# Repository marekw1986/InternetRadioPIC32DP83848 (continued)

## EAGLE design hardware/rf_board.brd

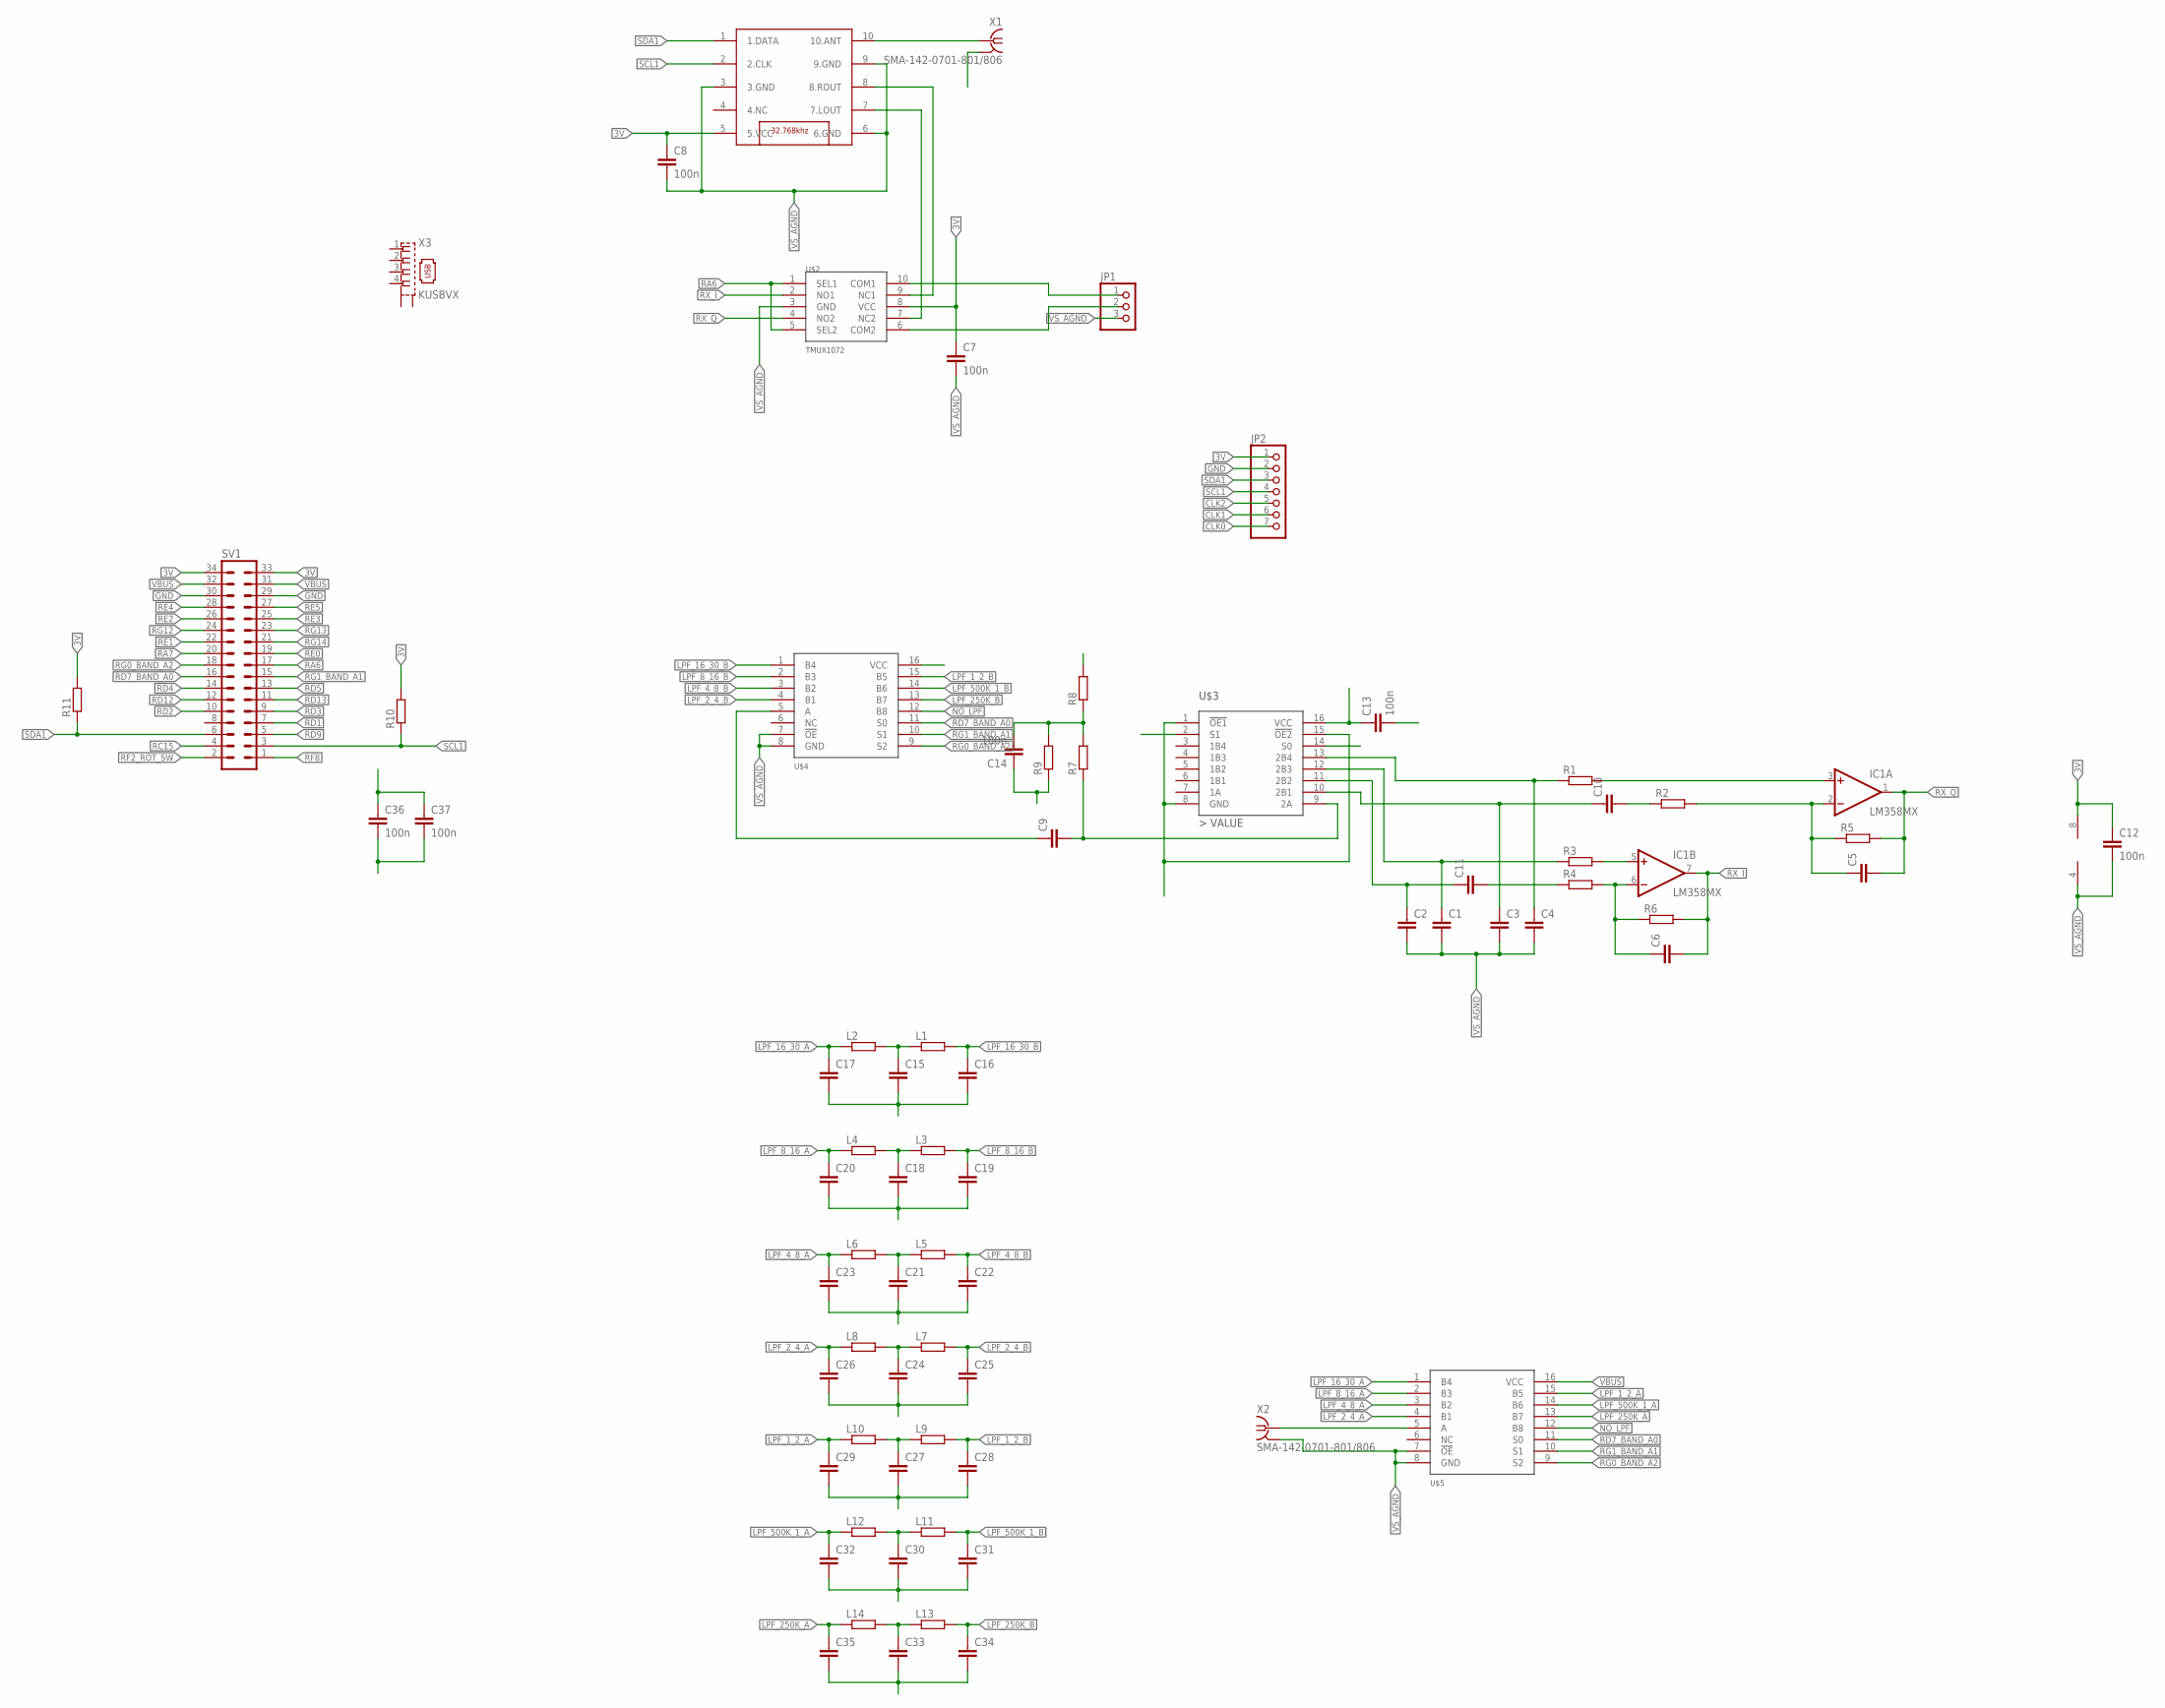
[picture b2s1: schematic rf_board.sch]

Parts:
C1, C2, C3, C4, C5, C6, C9, C10, C11: C-EUC0603; C0603
C7: 100n; C1206
C8, C12, C13, C14, C36, C37: 100n; C0603
C15, C16, C17, C18, C19, C20, C21, C22, C23, C24, C25, C26, C27, C28, C29, C30, C31, C32, C33, C34, C35: C-EUC0805; C0805
IC1: LM358MX; SO08
JP1: PINHD-1X3; 1X03
JP2: PINHD-1X7; 1X07
L1, L2, L3, L4, L5, L6, L7, L8, L9, L10, L11, L12, L13, L14: R-EU_R0805; R0805
R1, R2, R3, R4, R5, R6, R8, R9: R-EU_R0603; R0603
R7, R11: R-EU_0204/5; 0204/5
R10: R-EU_0204/7; 0204/7
SV1: ML34L
U$1: TEA5767; TJ-102BC
U$2: TMUX1072; TSSOP8
U$3: FST3253SO16; SO16
U$4, U$5: SN74CBT3251; TSSOP16
X1, X2: SMA-142-0701-801/806; J502-ND-142-0701-801/806
X3: KUSBVX

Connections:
3V: C7.1, C8.1, C12.1, C13.1, IC1.8 (V+), JP2.1, R8.2, R10.2, R11.2, SV1.33, SV1.34, U$1.5 (5.VCC), U$2.8 (VCC), U$3.16 (VCC)
CLK0: JP2.7, U$3.14 (S0)
CLK1: JP2.6, U$3.2 (S1)
CLK2: JP2.5
GND: JP2.2, SV1.29, SV1.30
IN_LEFT: JP1.2, U$2.6 (COM2)
IN_RIGHT: JP1.1, U$2.10 (COM1)
LPF_1_2_A: C29.1, L10.1, U$5.15 (B5)
LPF_1_2_B: C28.1, L9.2, U$4.15 (B5)
LPF_2_4_A: C26.1, L8.1, U$5.4 (B1)
LPF_2_4_B: C25.1, L7.2, U$4.4 (B1)
LPF_4_8_A: C23.1, L6.1, U$5.3 (B2)
LPF_4_8_B: C22.1, L5.2, U$4.3 (B2)
LPF_8_16_A: C20.1, L4.1, U$5.2 (B3)
LPF_8_16_B: C19.1, L3.2, U$4.2 (B3)
LPF_16_30_A: C17.1, L2.1, U$5.1 (B4)
LPF_16_30_B: C16.1, L1.2, U$4.1 (B4)
LPF_250K_A: C35.1, L14.1, U$5.13 (B7)
LPF_250K_B: C34.1, L13.2, U$4.13 (B7)
LPF_500K_1_A: C32.1, L12.1, U$5.14 (B6)
LPF_500K_1_B: C31.1, L11.2, U$4.14 (B6)
unnamed: IC1.3 (+IN), R1.2
unnamed: C3.1, C10.1, U$3.10 (2B1)
unnamed: C4.1, R1.1, U$3.13 (2B4)
unnamed: C1.1, R3.1, U$3.12 (2B3)
unnamed: C2.1, C11.1, U$3.11 (2B2)
unnamed: C5.1, IC1.2 (-IN), R2.2, R5.1
unnamed: IC1.5 (+IN), R3.2
unnamed: C6.1, IC1.6 (-IN), R4.2, R6.1
unnamed: C9.2, R7.1, U$3.9 (2A)
unnamed: U$1.8 (8.ROUT), U$2.9 (NC1)
unnamed: U$1.7 (7.LOUT), U$2.7 (NC2)
unnamed: C10.2, R2.1
unnamed: C11.2, R4.1
unnamed: C14.2, R7.2, R8.1, R9.2
unnamed: C15.1, L1.1, L2.2
unnamed: U$5.5 (A), X2.1
unnamed: U$1.10 (10.ANT), X1.1
unnamed: C18.1, L3.1, L4.2
unnamed: C21.1, L5.1, L6.2
unnamed: C24.1, L7.1, L8.2
unnamed: C27.1, L9.1, L10.2
unnamed: C30.1, L11.1, L12.2
unnamed: C33.1, L13.1, L14.2
unnamed: C9.1, U$4.5 (A)
NO_LPF: U$4.12 (B8), U$5.12 (B8)
RA6: SV1.17, U$2.1 (SEL1), U$2.5 (SEL2)
RA7: SV1.20
RC15: SV1.4
RD1: SV1.7
RD2: SV1.10
RD3: SV1.9
RD4: SV1.14
RD5: SV1.13
RD7_BAND_A0: SV1.16, U$4.11 (S0), U$5.11 (S0)
RD9: SV1.5
RD12: SV1.12
RD13: SV1.11
RE0: SV1.19
RE1: SV1.22
RE2: SV1.26
RE3: SV1.25
RE4: SV1.28
RE5: SV1.27
RF2_ROT_SW: SV1.2
RF8: SV1.1
RG0_BAND_A2: SV1.18, U$4.9 (S2), U$5.9 (S2)
RG1_BAND_A1: SV1.15, U$4.10 (S1), U$5.10 (S1)
RG12: SV1.24
RG13: SV1.23
RG14: SV1.21
RX_I: C6.2, IC1.7 (OUT), R6.2, U$2.2 (NO1)
RX_Q: C5.2, IC1.1 (OUT), R5.2, U$2.4 (NO2)
SCL1: JP2.4, R10.1, SV1.3, U$1.2 (2.CLK)
SDA1: JP2.3, R11.1, SV1.6, U$1.1 (1.DATA)
VBUS: C36.1, C37.1, SV1.31, SV1.32, U$4.16 (VCC), U$5.16 (VCC)
VS_AGND: C1.2, C2.2, C3.2, C4.2, C7.2, C8.2, C12.2, C13.2, C14.1, C15.2, C16.2, C17.2, C18.2, C19.2, C20.2, C21.2, C22.2, C23.2, C24.2, C25.2, C26.2, C27.2, C28.2, C29.2, C30.2, C31.2, C32.2, C33.2, C34.2, C35.2, C36.2, C37.2, IC1.4 (V-), JP1.3, R9.1, U$1.3 (3.GND), U$1.6 (6.GND), U$1.9 (9.GND), U$2.3 (GND), U$3.1 (!OE1), U$3.8 (GND), U$3.15 (!OE2), U$4.7 (!OE), U$4.8 (GND), U$5.7 (!OE), U$5.8 (GND), X1.G@1 (2), X1.G@2 (2), X1.G@3 (2), X1.G@4 (2), X2.G@1 (2), X2.G@2 (2), X2.G@3 (2), X2.G@4 (2)

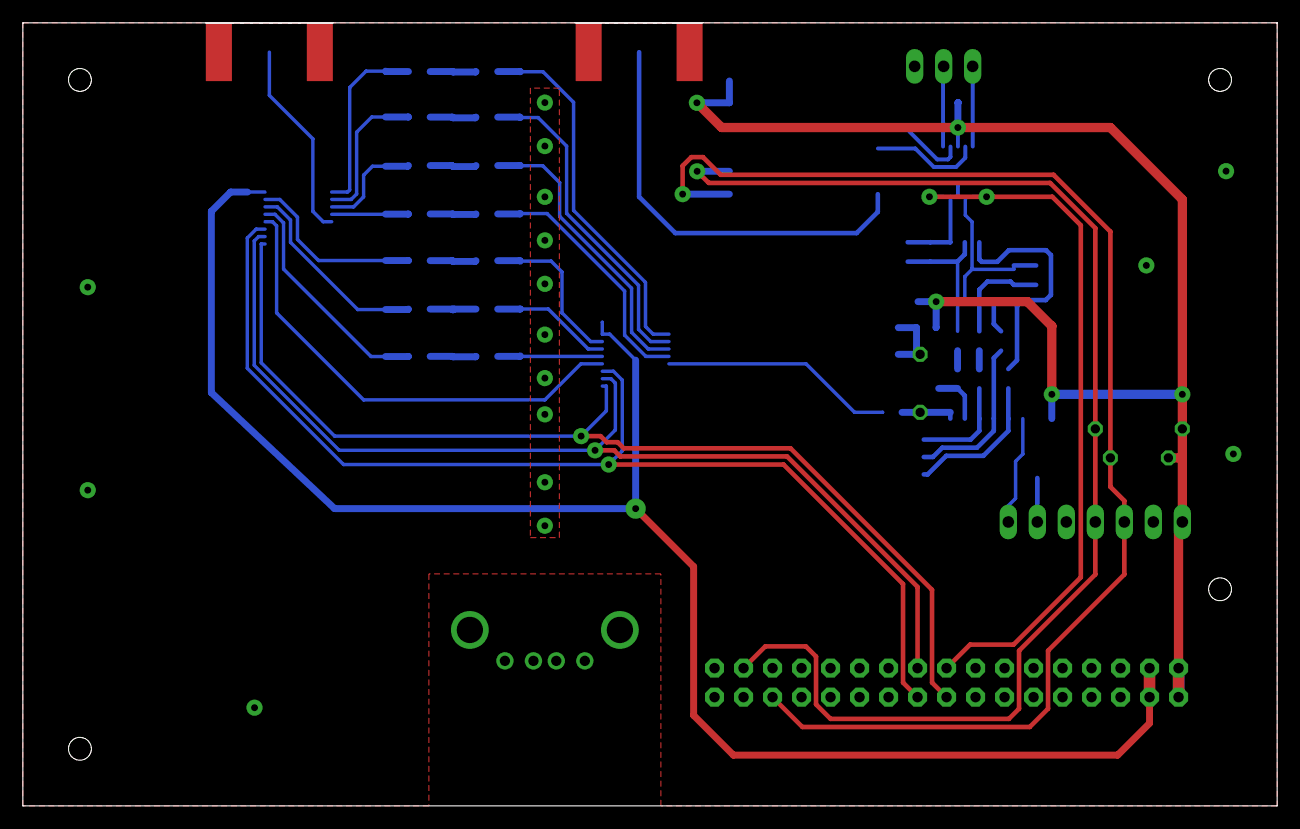
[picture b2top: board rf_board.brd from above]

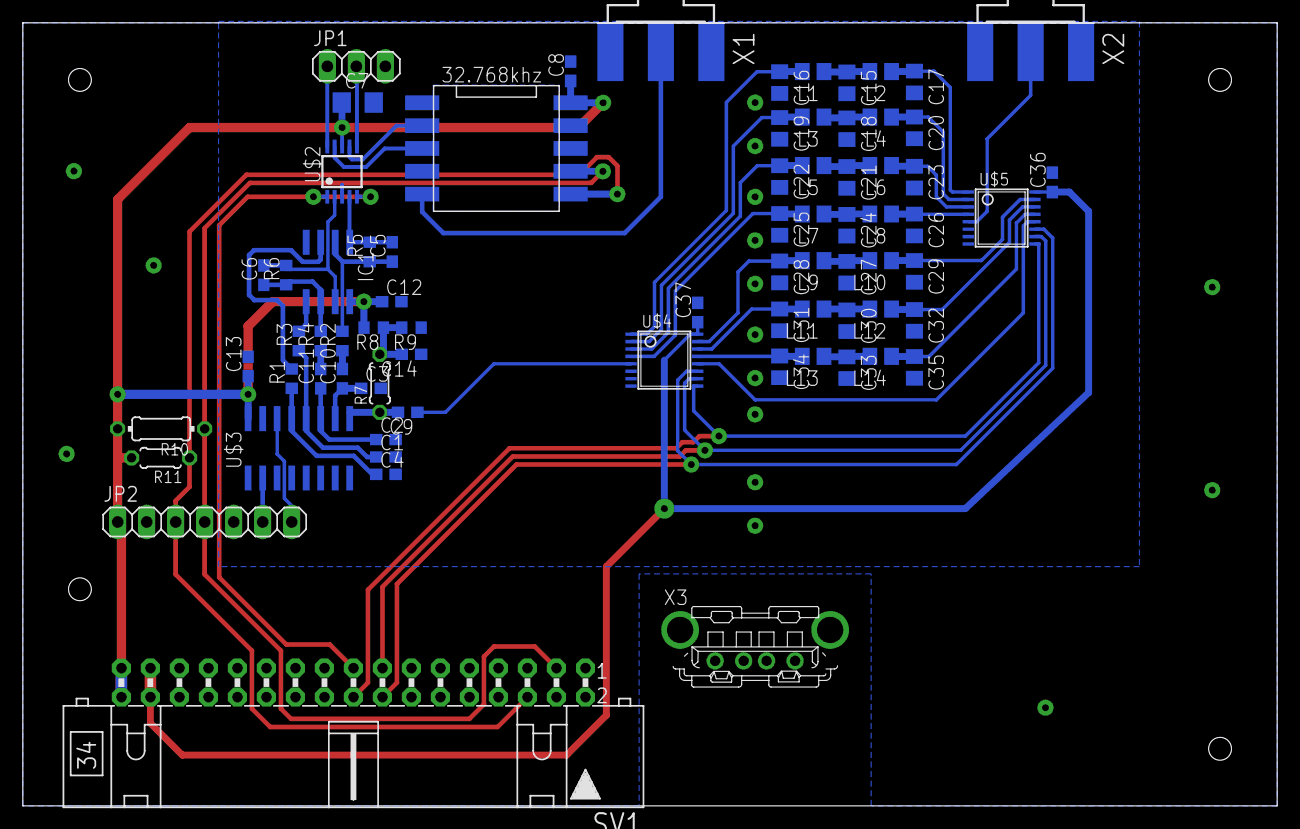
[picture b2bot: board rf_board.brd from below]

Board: 2 copper layers, 109.9 x 68.6 mm, 74 parts (74 on the bottom side), 55 nets.

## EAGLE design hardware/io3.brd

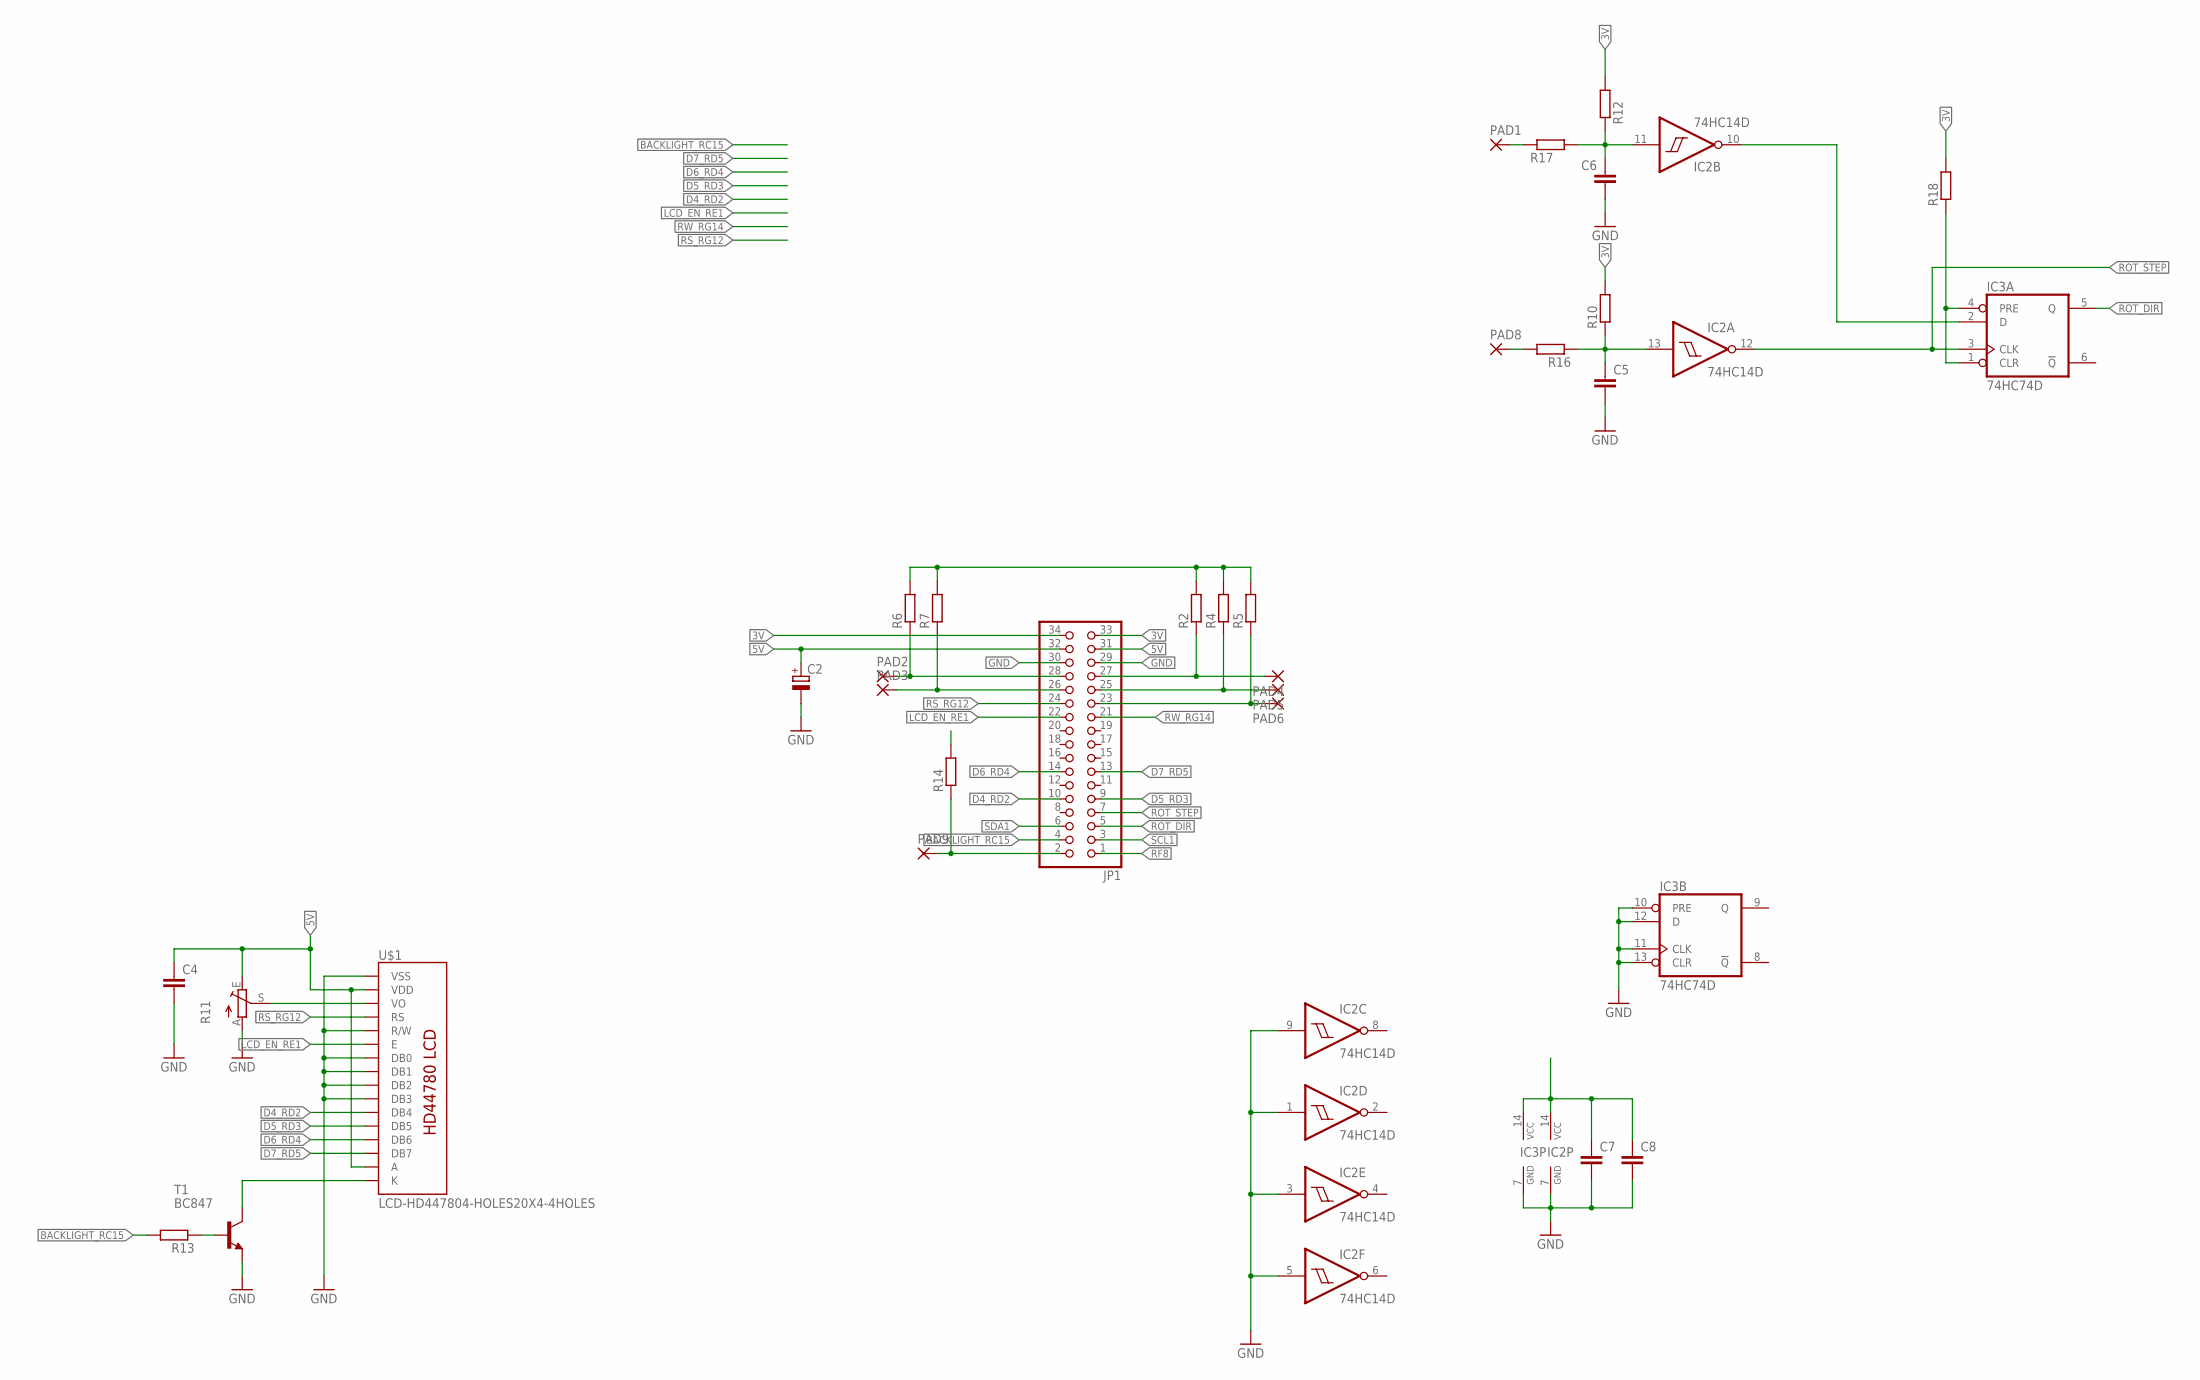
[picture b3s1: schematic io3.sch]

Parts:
C2: CPOL-EUSMCD; SMC_D
C4: C-EUC1206; C1206
C5, C6, C7, C8: C-EUC0603; C0603
IC2: 74HC14D; SO14
IC3: 74HC74D; SO14
JP1: PINHD-2X17_2.54-SMD; 2X17SMD
PAD1, PAD2, PAD3, PAD4, PAD5, PAD6, PAD8, PAD9: SMD2; SMD1,27-2,54
R2, R4, R5, R6, R7, R10, R12, R18: R-EU_0204/7; 0204/7
R11: TRIM_EU-B25U; B25U
R13, R14: R-EU_0204/5; 0204/5
R16, R17: R-EU_R0603; R0603
T1: BC847; SOT23
U$1: LCD-HD447804-HOLES20X4-4HOLES; LCD-20X4-4HOLES

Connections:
3V: C7.1, C8.1, IC2.14 (VCC), IC3.14 (VCC), JP1.33, JP1.34, R2.2, R4.2, R5.2, R6.2, R7.2, R10.2, R12.2, R14.2, R18.2
5V: C2.+, C4.1, JP1.31, JP1.32, R11.E, U$1.P$2 (VDD), U$1.P$15 (A)
BACKLIGHT_RC15: JP1.4, R13.2
D4_RD2: JP1.10, U$1.P$11 (DB4)
D5_RD3: JP1.9, U$1.P$12 (DB5)
D6_RD4: JP1.14, U$1.P$13 (DB6)
D7_RD5: JP1.13, U$1.P$14 (DB7)
GND: C2.-, C4.2, C5.2, C6.2, C7.2, C8.2, IC2.1 (I), IC2.3 (I), IC2.5 (I), IC2.7 (GND), IC2.9 (I), IC3.7 (GND), IC3.10 (PRE), IC3.11 (CLK), IC3.12 (D), IC3.13 (CLR), JP1.29, JP1.30, R11.A, T1.2 (E), U$1.P$1 (VSS), U$1.P$5 (R/W), U$1.P$7 (DB0), U$1.P$8 (DB1), U$1.P$9 (DB2), U$1.P$10 (DB3)
LCD_EN_RE1: JP1.22, U$1.P$6 (E)
unnamed: T1.3 (C), U$1.P$16 (K)
unnamed: IC3.1 (CLR), IC3.4 (PRE), R18.1
unnamed: PAD8.1, R16.2
unnamed: R13.1, T1.1 (B)
unnamed: PAD1.1, R17.1
unnamed: R11.S, U$1.P$3 (VO)
RF8: JP1.1
ROT_A_DT: C5.1, IC2.13 (I), R10.1, R16.1
ROT_B_: IC2.10 (O), IC3.2 (D)
ROT_B_CLK: C6.1, IC2.11 (I), R12.1, R17.2
ROT_DIR: IC3.5 (Q), JP1.5
ROT_STEP: IC2.12 (O), IC3.3 (CLK), JP1.7
ROT_SW: JP1.2, PAD9.1, R14.1
RS_RG12: JP1.24, U$1.P$4 (RS)
RW_RG14: JP1.21
S1: JP1.27, PAD4.1, R2.1
S2: JP1.28, PAD2.1, R6.1
S3: JP1.25, PAD5.1, R4.1
S4: JP1.26, PAD3.1, R7.1
S5: JP1.23, PAD6.1, R5.1
SCL1: JP1.3
SDA1: JP1.6

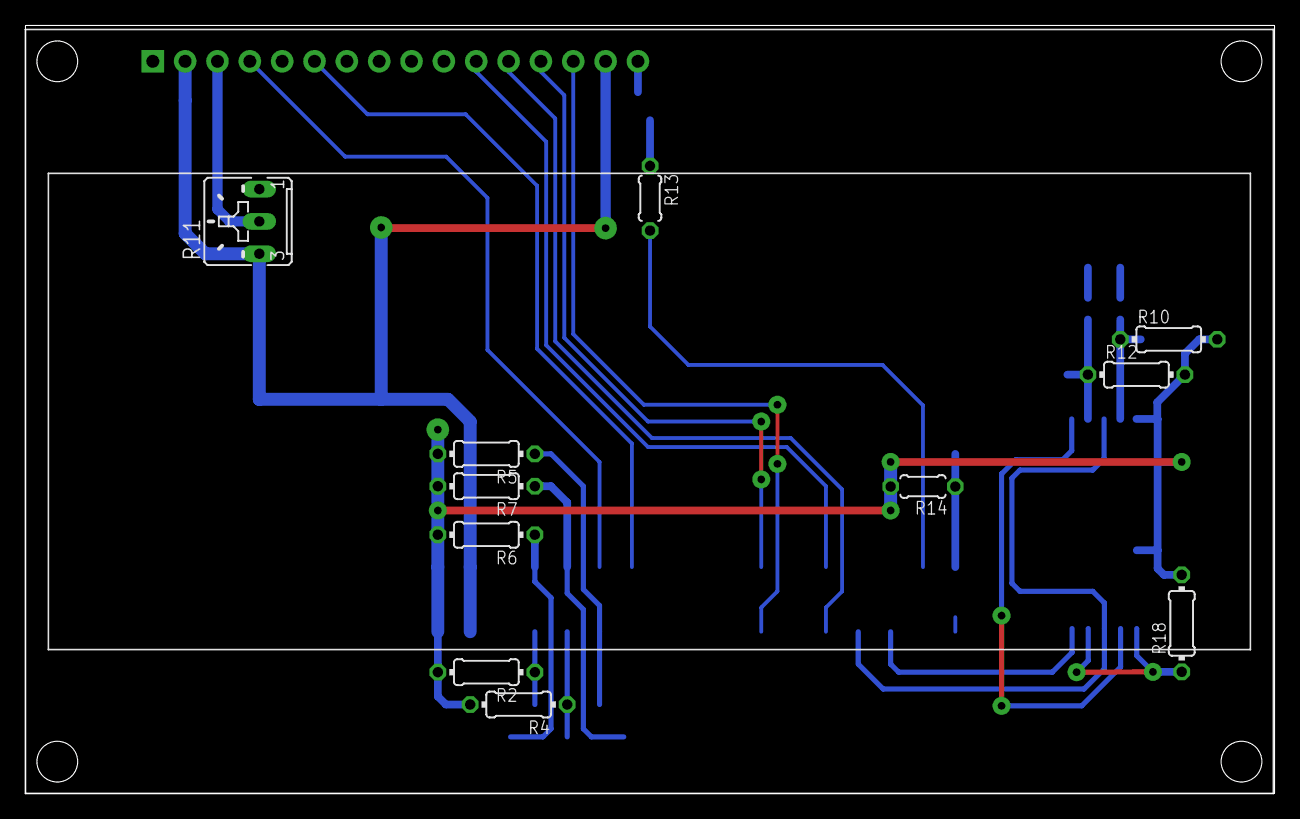
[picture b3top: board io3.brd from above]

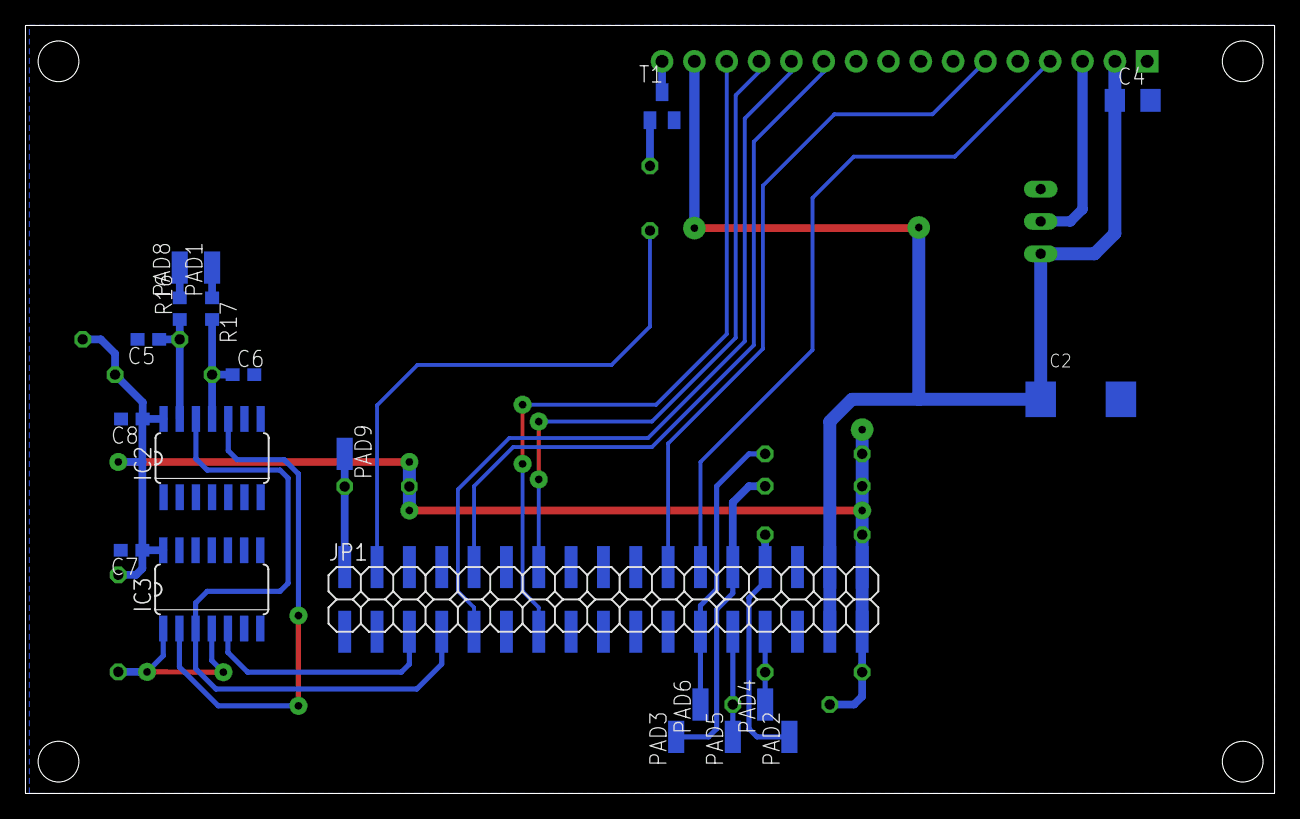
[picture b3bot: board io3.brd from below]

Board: 2 copper layers, 98.1 x 60.3 mm, 32 parts (20 on the bottom side), 27 nets.

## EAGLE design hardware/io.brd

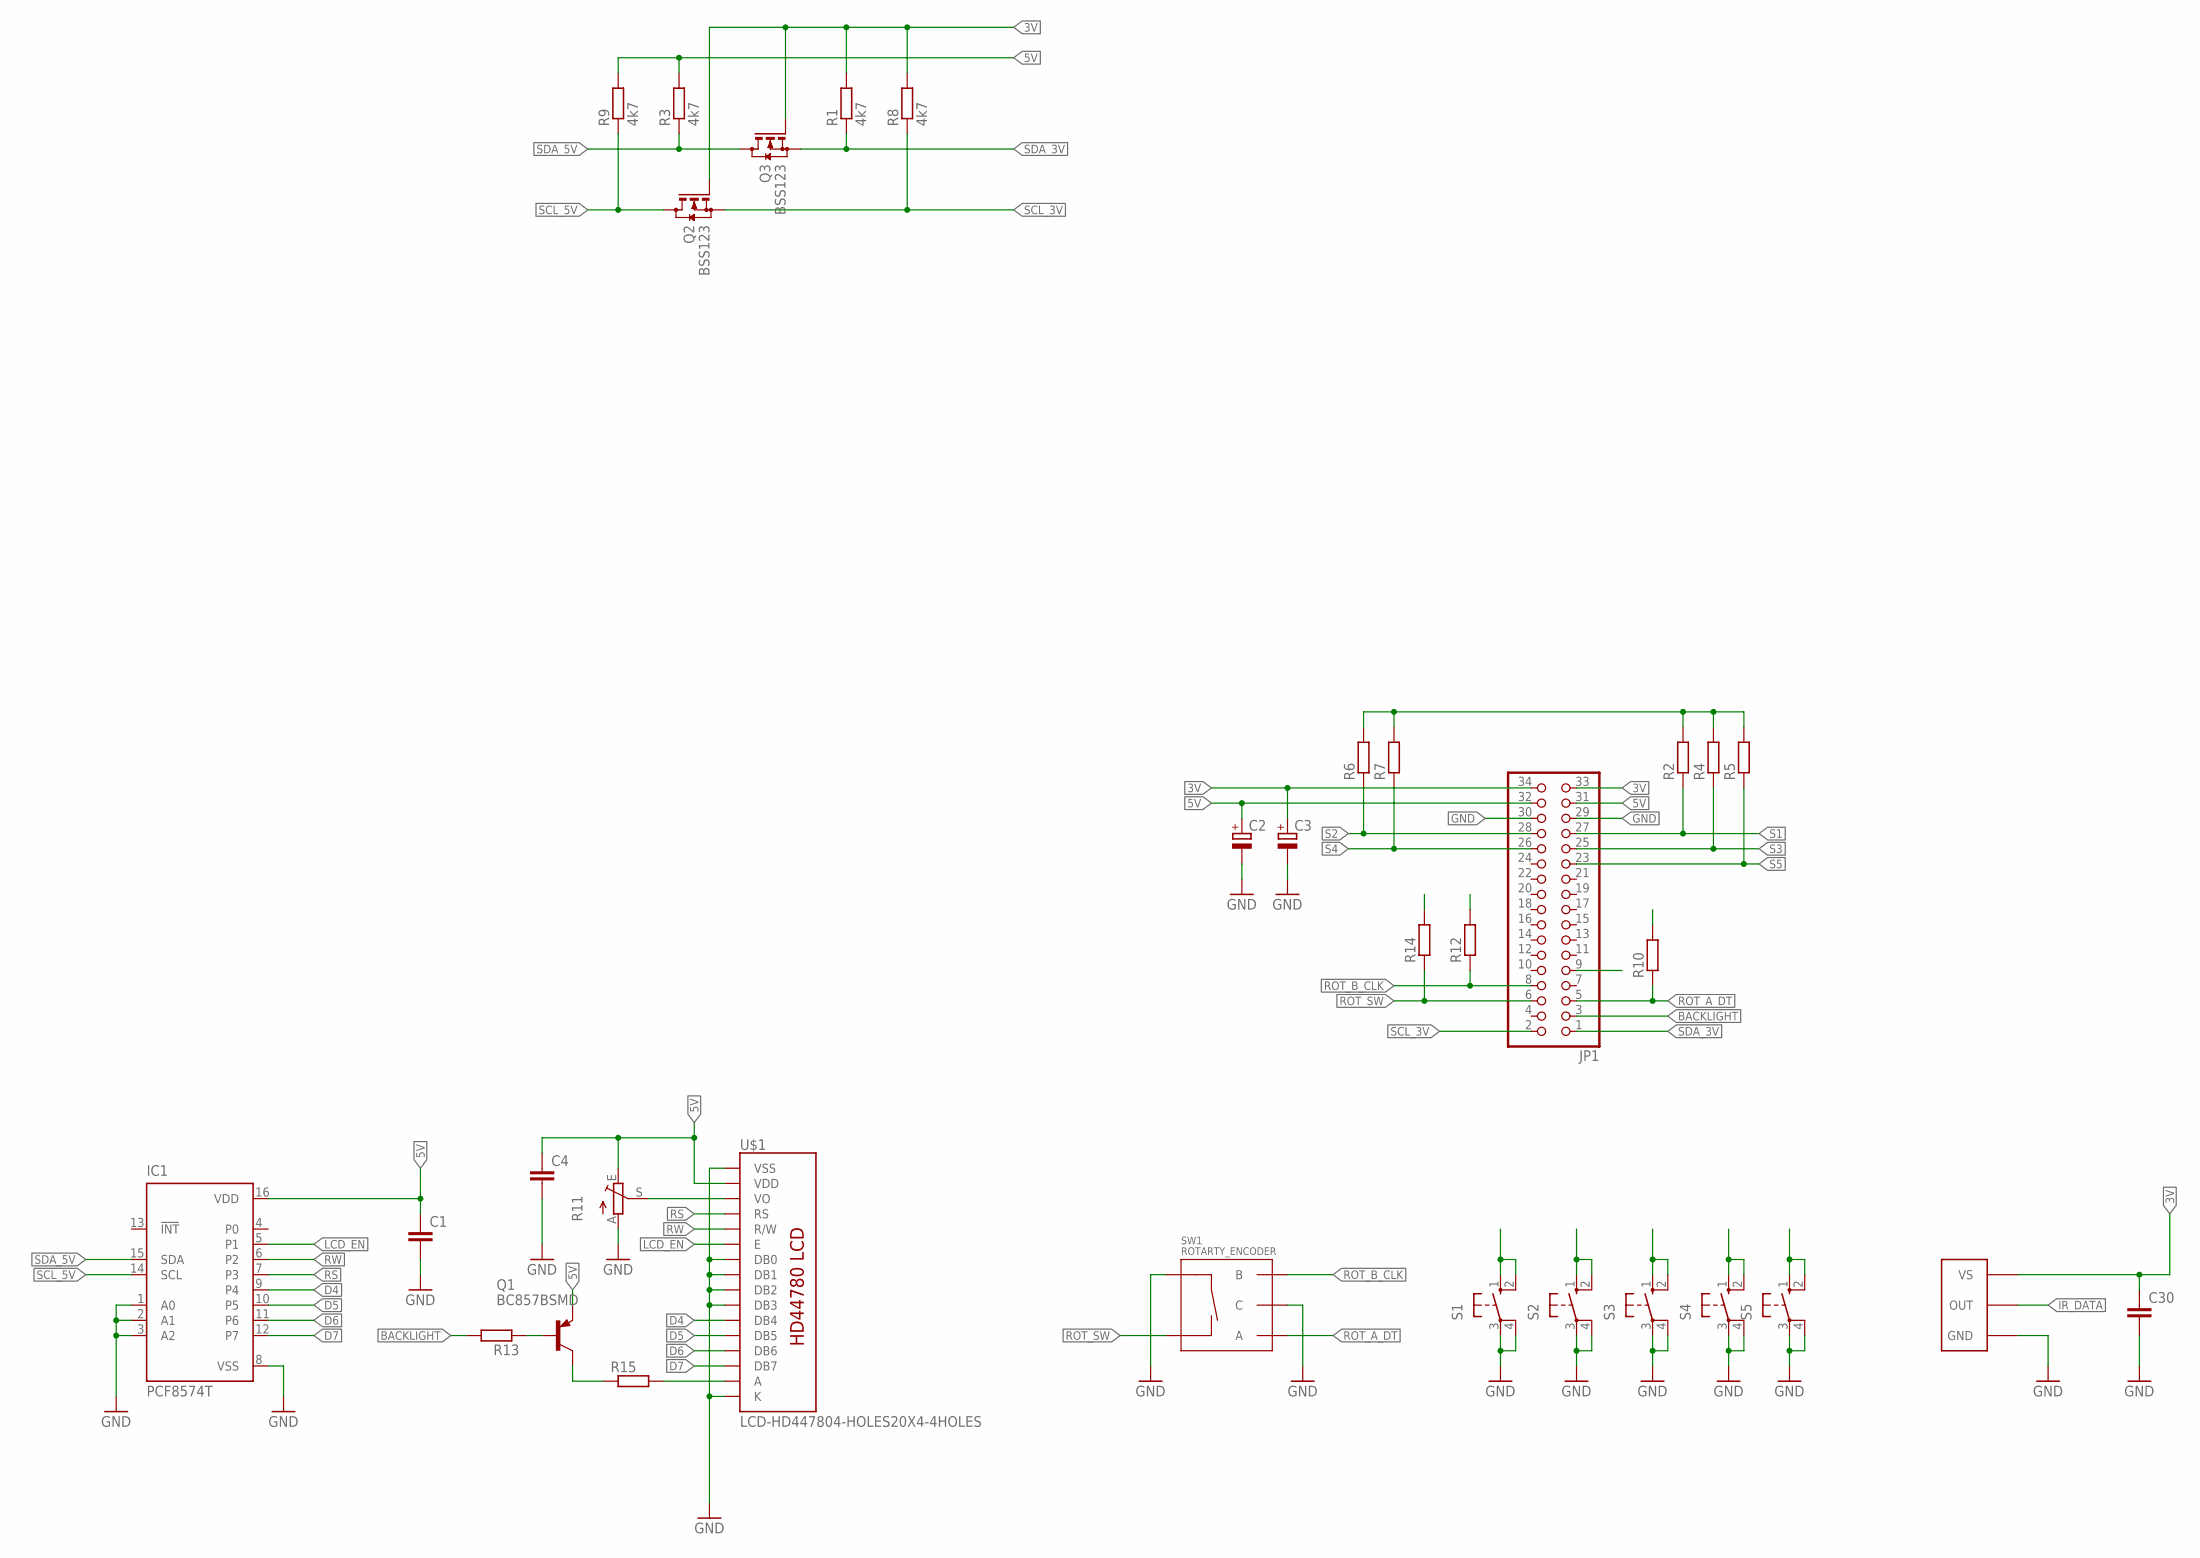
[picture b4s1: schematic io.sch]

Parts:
C1: C-EUC0603; C0603
C2: CPOL-EUSMCD; SMC_D
C3: CPOL-EUSMCB; SMC_B
C4, C30: C-EUC1206; C1206
IC1: PCF8574T; SO16W
JP1: PINHD-2X17_2.54-SMD; 2X17SMD
Q1: BC857BSMD; SOT23-BEC
Q2, Q3: BSS123; SOT23
R1, R3, R8, R9: 4k7; R0603
R2, R4, R5, R6, R7, R10, R12, R13, R14: R-EU_0204/7; 0204/7
R11: TRIM_EU-B25U; B25U
R15: R-EU_R0603; R0603
S1, S2, S3, S4, S5: 40-XX; B3F-40XX
SW1: ROTARTY_ENCODER; ROTARY_ENC_PLAIN
U$1: LCD-HD447804-HOLES20X4-4HOLES; LCD-20X4-4HOLES
U$5: TSOP312XVERTICAL; TSOP312X_VERT

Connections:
3V: C3.+, C30.1, JP1.33, JP1.34, Q2.1 (G), Q3.1 (G), R1.2, R2.2, R4.2, R5.2, R6.2, R7.2, R8.2, R10.2, R12.2, R14.2, U$5.2 (VS)
5V: C1.1, C2.+, C4.1, IC1.16 (VDD), JP1.31, JP1.32, Q1.E, R3.2, R9.2, R11.E, U$1.P$2 (VDD)
BACKLIGHT: JP1.3, R13.2
D4: IC1.9 (P4), U$1.P$11 (DB4)
D5: IC1.10 (P5), U$1.P$12 (DB5)
D6: IC1.11 (P6), U$1.P$13 (DB6)
D7: IC1.12 (P7), U$1.P$14 (DB7)
GND: C1.2, C2.-, C3.-, C4.2, C30.2, IC1.1 (A0), IC1.2 (A1), IC1.3 (A2), IC1.8 (VSS), JP1.29, JP1.30, R11.A, S1.3, S1.4 (P1), S2.3, S2.4 (P1), S3.3, S3.4 (P1), S4.3, S4.4 (P1), S5.3, S5.4 (P1), SW1.C, SW1.SW+, U$1.P$1 (VSS), U$1.P$7 (DB0), U$1.P$8 (DB1), U$1.P$9 (DB2), U$1.P$10 (DB3), U$1.P$16 (K), U$5.1 (GND)
IR_DATA: JP1.9, U$5.3 (OUT)
LCD_EN: IC1.5 (P1), U$1.P$6 (E)
unnamed: Q1.C, R15.1
unnamed: R15.2, U$1.P$15 (A)
unnamed: Q1.B, R13.1
unnamed: R11.S, U$1.P$3 (VO)
ROT_A_DT: JP1.5, R10.1, SW1.A
ROT_B_CLK: JP1.8, R12.1, SW1.B
ROT_SW: JP1.6, R14.1, SW1.SW-
RS: IC1.7 (P3), U$1.P$4 (RS)
RW: IC1.6 (P2), U$1.P$5 (R/W)
S1: JP1.27, R2.1, S1.1 (S), S1.2 (S1)
S2: JP1.28, R6.1, S2.1 (S), S2.2 (S1)
S3: JP1.25, R4.1, S3.1 (S), S3.2 (S1)
S4: JP1.26, R7.1, S4.1 (S), S4.2 (S1)
S5: JP1.23, R5.1, S5.1 (S), S5.2 (S1)
SCL_3V: JP1.2, Q2.2 (S), R8.1
SCL_5V: IC1.14 (SCL), Q2.3 (D), R9.1
SDA_3V: JP1.1, Q3.2 (S), R1.1
SDA_5V: IC1.15 (SDA), Q3.3 (D), R3.1

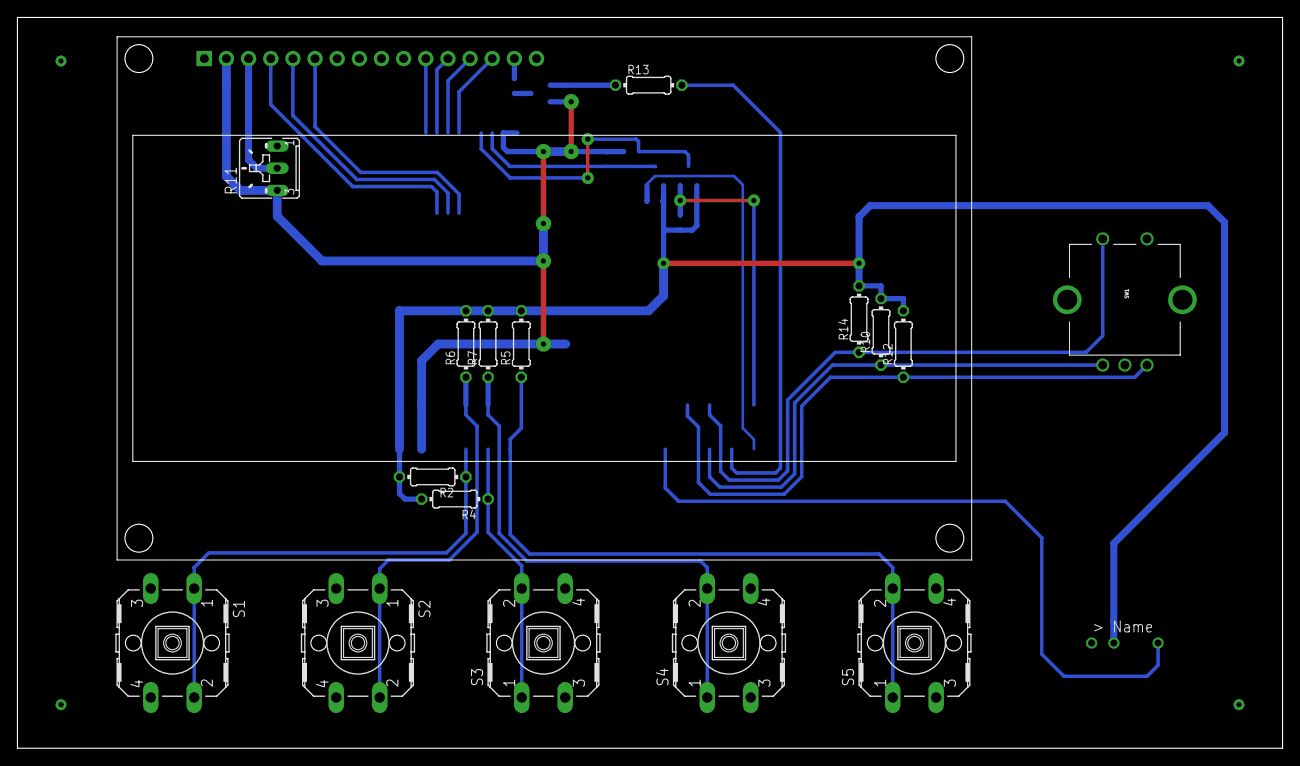
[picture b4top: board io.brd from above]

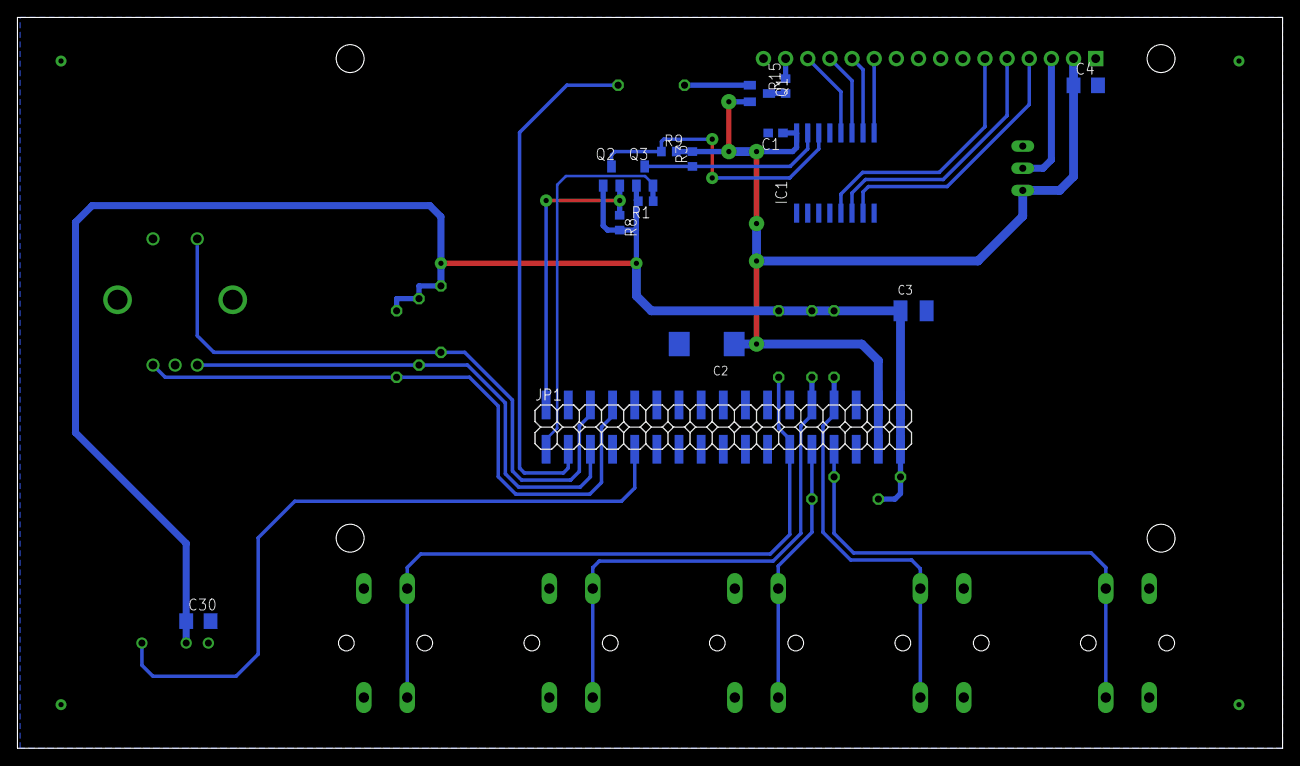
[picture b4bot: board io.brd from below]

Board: 2 copper layers, 145.1 x 83.8 mm, 33 parts (15 on the bottom side), 28 nets.
